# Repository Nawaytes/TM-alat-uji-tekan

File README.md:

# Alat Uji Tekan

Sebuah alat untuk menguji daya tahan benda terhadap tekanan. keyword: loadcell, stepper, hx711, rotary encoder

## Library Arduino

- #include "HX711.h" [link](https://github.com/bogde/HX711)
- #include <Encoder.h> [link](https://github.com/PaulStoffregen/Encoder)
- #include <AccelStepper.h> [link](https://www.airspayce.com/mikem/arduino/AccelStepper/index.html)

## Library Processing

- import processing.serial.Serial;
- import controlP5.*;

## Thanks to Curious Scientist
Best code for Accell Stepper using Serial [link](https://curiousscientist.tech/blog/arduino-accelstepper-tb6600-stepper-motor).  
Youtube Channel [link](https://www.youtube.com/channel/UCKp1MzuAceJnDqAvsZl_46g).  
Website [link](https://curiousscientist.tech/).  
## Desain GUI

## Desain Hardware

## Desain Mekanik

## License
[MIT](https://choosealicense.com/licenses/mit/)

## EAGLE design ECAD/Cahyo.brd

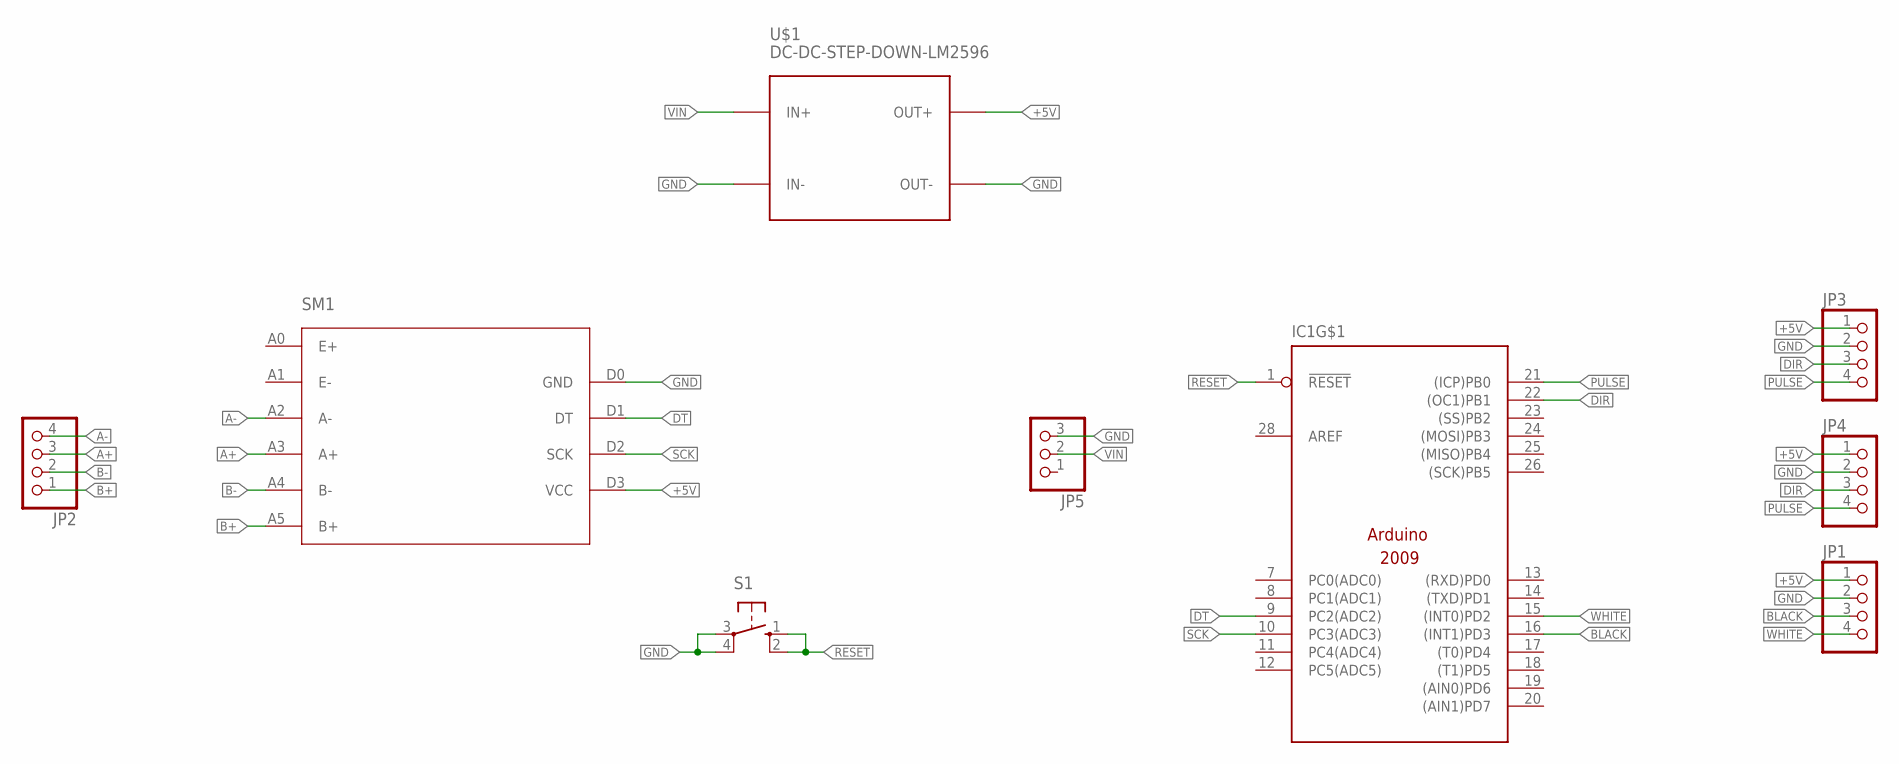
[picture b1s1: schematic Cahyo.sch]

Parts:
IC1: ARDUINO2009_PIN_22; ARDUINO2009_2
JP1, JP2, JP3, JP4: PINHD-1X4; 1X04
JP5: PINHD-1X3; 1X03
S1: 10-XX; B3F-10XX
SM1: HX711
U$1: DC-DC-STEP-DOWN-LM2596

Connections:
+3V3: IC1.2 (+3V3)
+5V: IC1.3 (+5V), JP1.1, JP3.1, JP4.1, SM1.D3 (VCC), U$1.OUT+
A+: JP2.3, SM1.A3 (A+)
A-: JP2.4, SM1.A2 (A-)
B+: JP2.1, SM1.A5 (B+)
B-: JP2.2, SM1.A4 (B-)
BLACK: IC1.16 ((INT1)PD3), JP1.3
DIR: IC1.22 ((OC1)PB1), JP3.3, JP4.3
DT: IC1.9 (PC2(ADC2)), SM1.D1 (DT)
GND: IC1.4 (GND), IC1.5 (GND), IC1.27 (GND), JP1.2, JP3.2, JP4.2, JP5.3, S1.3, S1.4 (P1), SM1.D0 (GND), U$1.IN-, U$1.OUT-
PULSE: IC1.21 ((ICP)PB0), JP3.4, JP4.4
RESET: IC1.1 (!RESET), S1.1 (S), S1.2 (S1)
SCK: IC1.10 (PC3(ADC3)), SM1.D2 (SCK)
VIN: IC1.6 (+VIN), JP5.2, U$1.IN+
WHITE: IC1.15 ((INT0)PD2), JP1.4

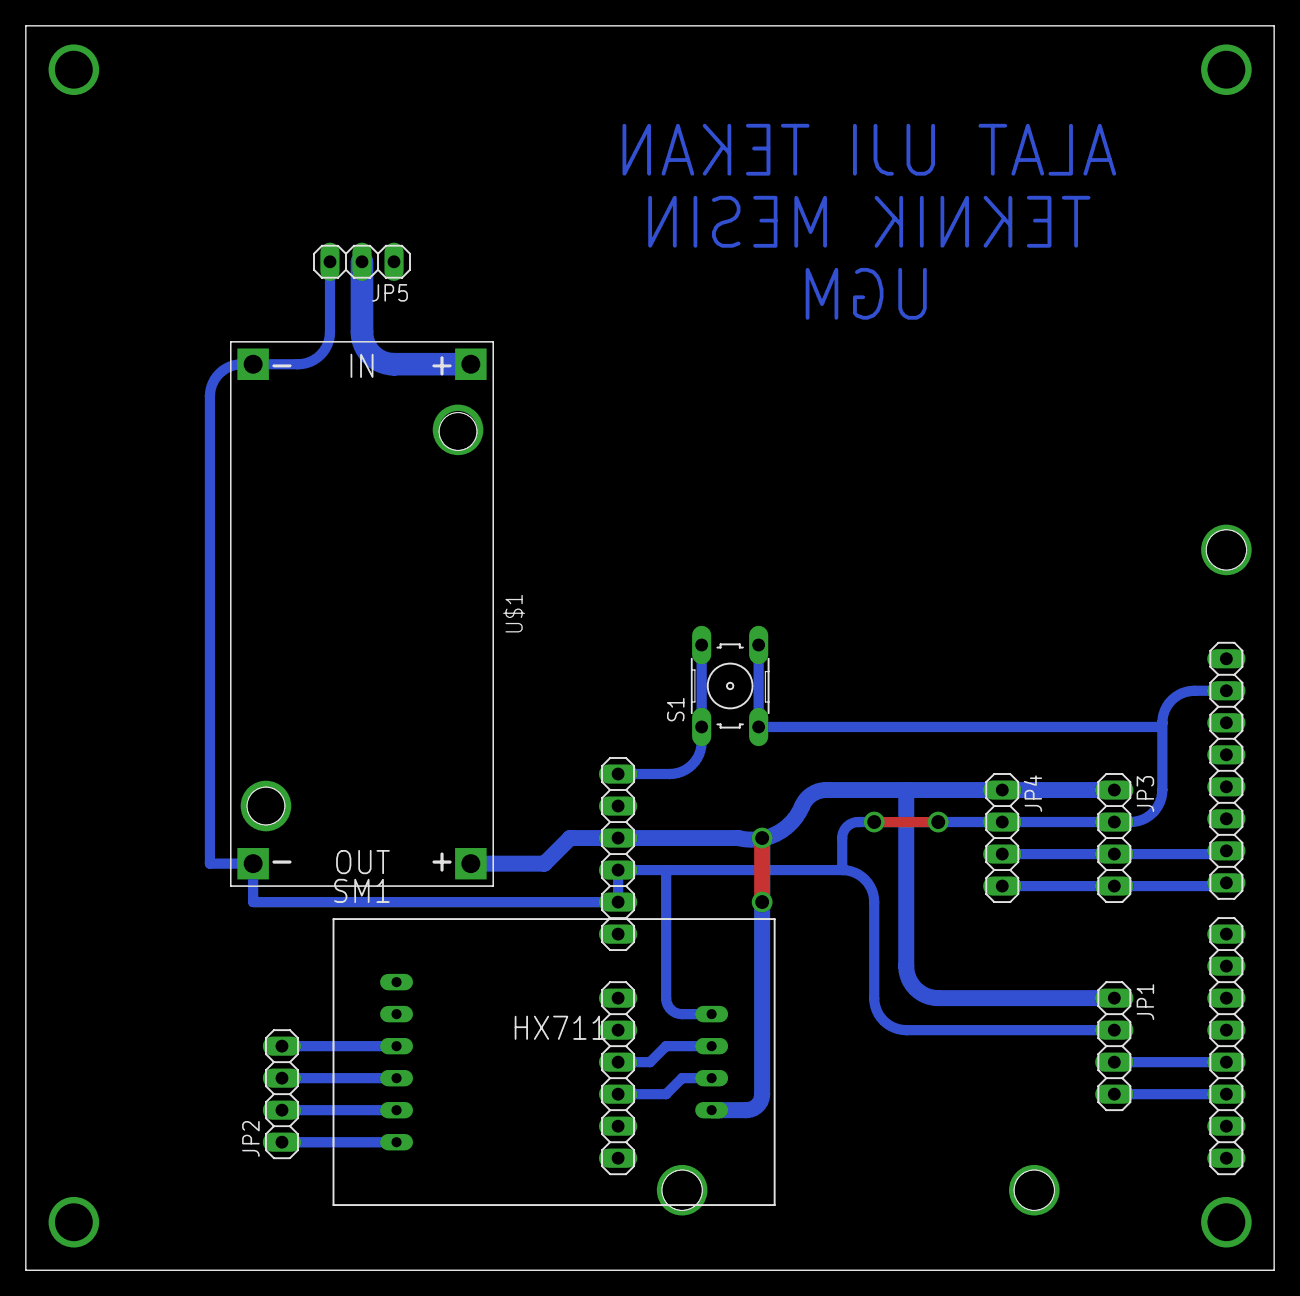
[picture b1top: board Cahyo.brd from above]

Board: 2 copper layers, 99.0 x 98.7 mm, 9 parts (0 on the bottom side), 14 nets.

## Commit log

2021-03-30 blank program
2021-04-02 ecad design
2021-04-02 bottom preview
2021-05-29 update gui mcad
2021-06-04 update GUI
2021-06-04 readme
2021-06-05 update config -
    "graph-range-l":0,
    "graph-range-h":10000,
    "graph-width":200

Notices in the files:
parts and their libraries:
diy-modules: Released under the Creative Commons Attribution 4.0 International License: http://creativecommons.org/licenses/by/4.0
